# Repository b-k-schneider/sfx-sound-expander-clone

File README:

SFX sound expander clone. Basically it is a YM3812 chip for the C64 home computer.

Original developer: Krzysztof Iwanowski

The PCB layouts and schematics are released under a Creative Commons cc-by-sa 3.0 license.

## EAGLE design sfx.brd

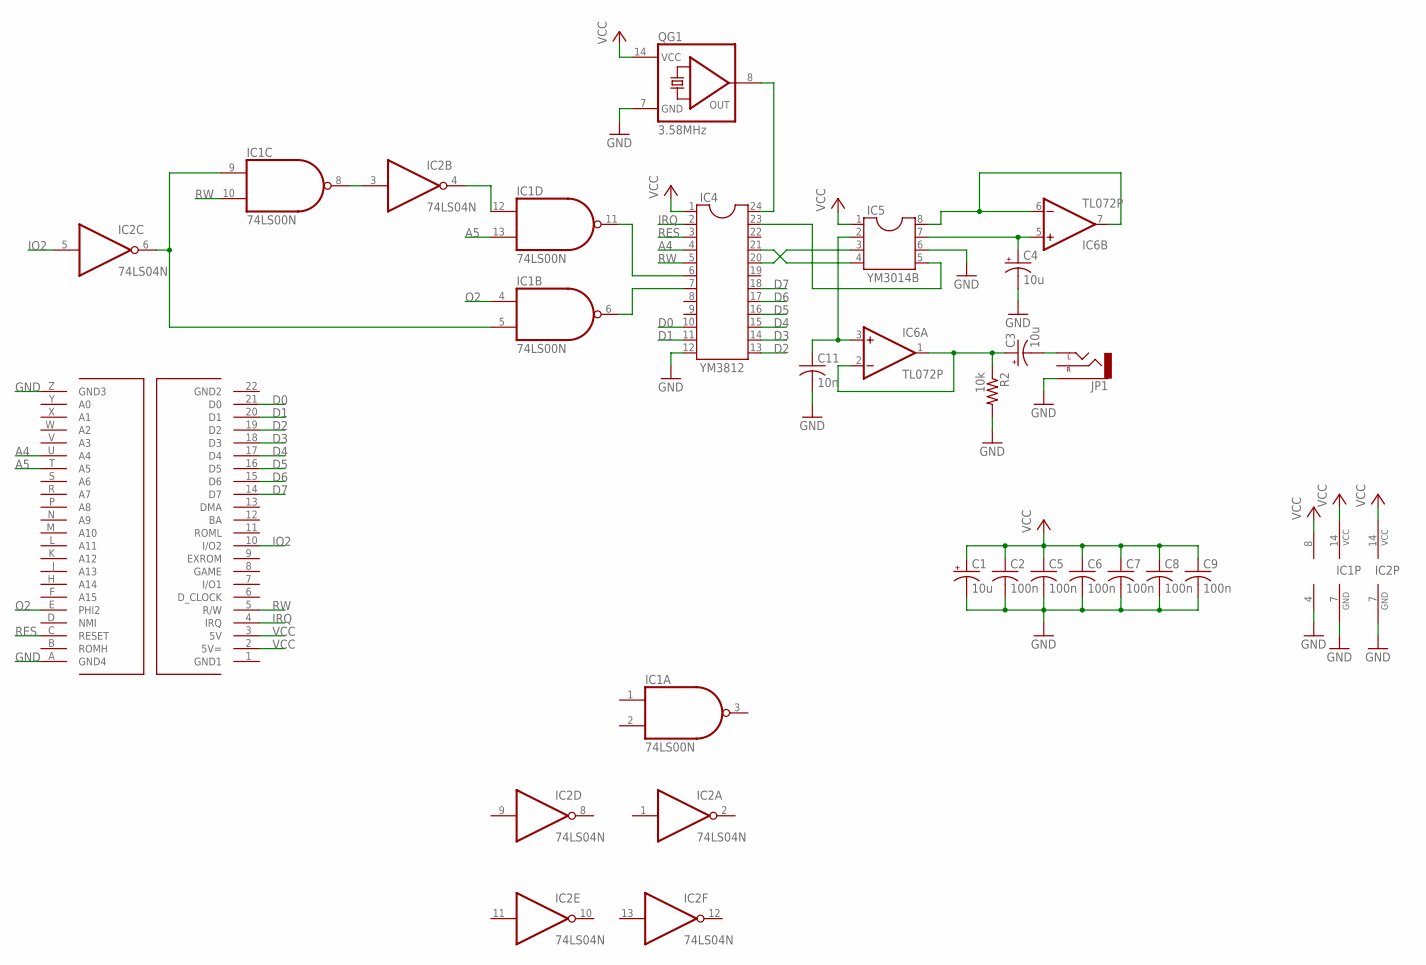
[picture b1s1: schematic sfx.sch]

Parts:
C1, C3, C4: 10u; E2,5-6
C2, C5, C6, C7, C8, C9: 100n; C025-025X050
C11: 10n; C025-025X050
IC1: 74LS00N; DIL14
IC2: 74LS04N; DIL14
IC4: YM3812; DIL24-6
IC5: YM3014B; DIL08
IC6: TL072P; DIL08
JP1: AUDIO-JACKPTH; AUDIO-JACK
QG1: 3.58MHz; DIL14S
R2: 10k; 0204/7
U$1: EASYFLASH_1.4.1_REV_B_C64_EXPANSION__CARTRIDGE

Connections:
A4: IC4.4, U$1.U (A4)
A5: IC1.13 (I1), U$1.T (A5)
D0: IC4.10, U$1.21 (D0)
D1: IC4.11, U$1.20 (D1)
D2: IC4.13, U$1.19 (D2)
D3: IC4.14, U$1.18 (D3)
D4: IC4.15, U$1.17 (D4)
D5: IC4.16, U$1.16 (D5)
D6: IC4.17, U$1.15 (D6)
D7: IC4.18, U$1.14 (D7)
GND: C1.-, C2.2, C4.-, C5.2, C6.2, C7.2, C8.2, C9.2, C11.2, IC1.7 (GND), IC2.7 (GND), IC4.12, IC5.6, IC6.4 (V-), JP1.SLEEVE, QG1.7 (GND), R2.2, U$1.A (GND4), U$1.Z (GND3)
IO2: IC2.5 (I), U$1.10 (I/O2)
IRQ: IC4.2, U$1.4 (IRQ)
unnamed: IC4.24, QG1.8 (OUT)
unnamed: IC4.23, IC5.5
unnamed: IC4.21, IC5.4
unnamed: IC4.20, IC5.3
unnamed: C11.1, IC5.2, IC6.3 (+IN)
unnamed: IC1.12 (I0), IC2.4 (O)
unnamed: IC1.11 (O), IC4.6
unnamed: IC1.6 (O), IC4.7
unnamed: IC5.8, IC6.6 (-IN), IC6.7 (OUT)
unnamed: IC1.8 (O), IC2.3 (I)
unnamed: IC1.5 (I1), IC1.9 (I0), IC2.6 (O)
unnamed: C3.-, JP1.TIP (LEFT)
unnamed: C4.+, IC5.7, IC6.5 (+IN)
unnamed: C3.+, IC6.1 (OUT), IC6.2 (-IN), R2.1
O2: IC1.4 (I0), U$1.E (PHI2)
RES: IC4.3, U$1.C (RESET)
RW: IC1.10 (I1), IC4.5, U$1.5 (R/W)
VCC: C1.+, C2.1, C5.1, C6.1, C7.1, C8.1, C9.1, IC1.14 (VCC), IC2.14 (VCC), IC4.1, IC5.1, IC6.8 (V+), QG1.14 (VCC), U$1.2 (5V=), U$1.3 (5V)

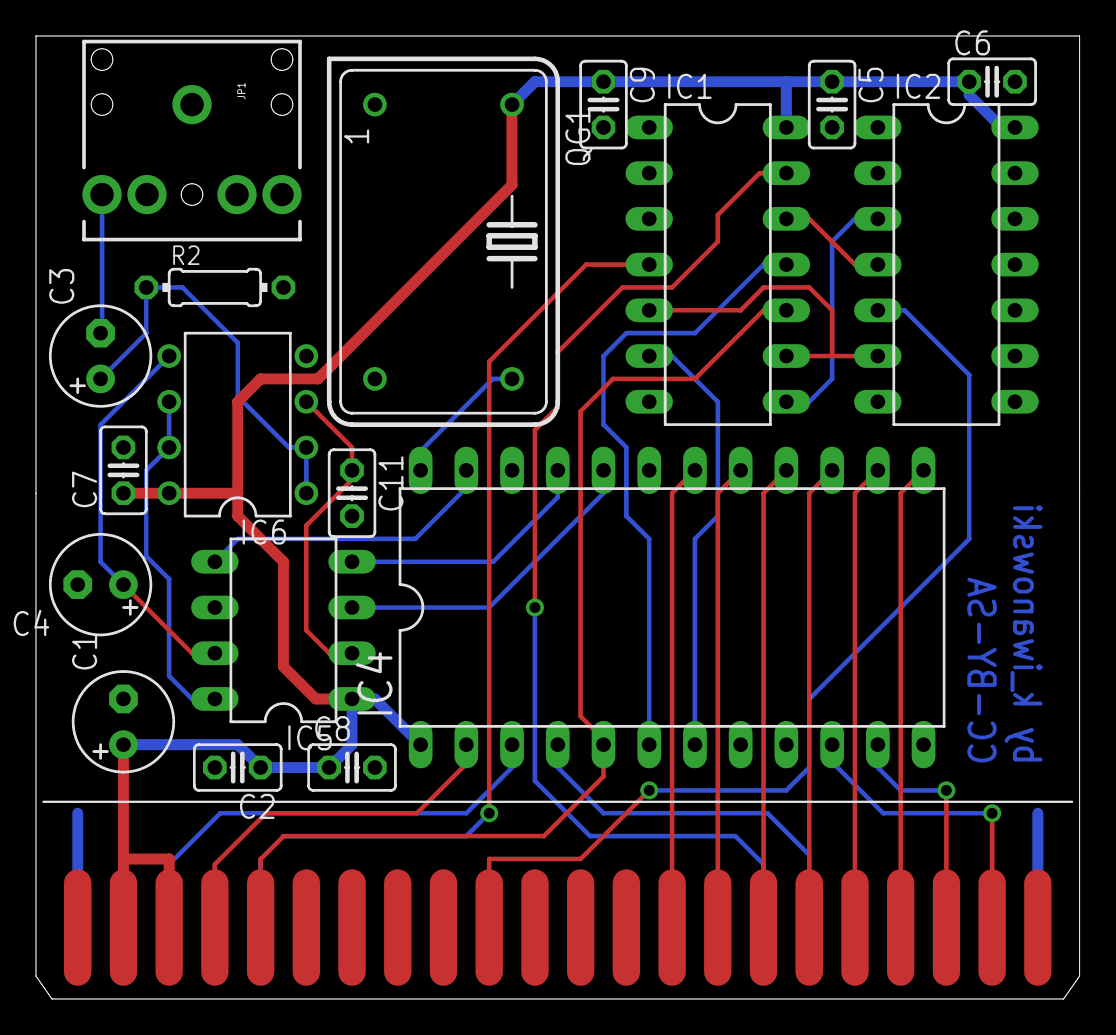
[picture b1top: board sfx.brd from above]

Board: 2 copper layers, 58.0 x 53.5 mm, 19 parts (0 on the bottom side), 31 nets.

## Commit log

2016-07-07 :octocat: Added .gitattributes & .gitignore files
2017-08-29 moved the audio jack

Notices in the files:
parts and their libraries:
SparkFun-Connectors: Licensing: Creative Commons ShareAlike 4.0 International - https://creativecommons.org/licenses/by-sa/4.0
